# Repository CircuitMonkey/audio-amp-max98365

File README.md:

# audio-amp-max98365
Class-D audio amplifier using the Maxim MAX98365.  I2S input, 18W output.

## Features
MAX98365 Class-D Amplifier chip.  14W Max.
Dimensions:  20mm x 13mm
5-14V Supply Voltage
I2S Signal Input

## Images

## See Maxim Datasheet for additional information
[https://datasheets.maximintegrated.com/en/ds/MAX98365.pdf](https://datasheets.maximintegrated.com/en/ds/MAX98365.pdf)

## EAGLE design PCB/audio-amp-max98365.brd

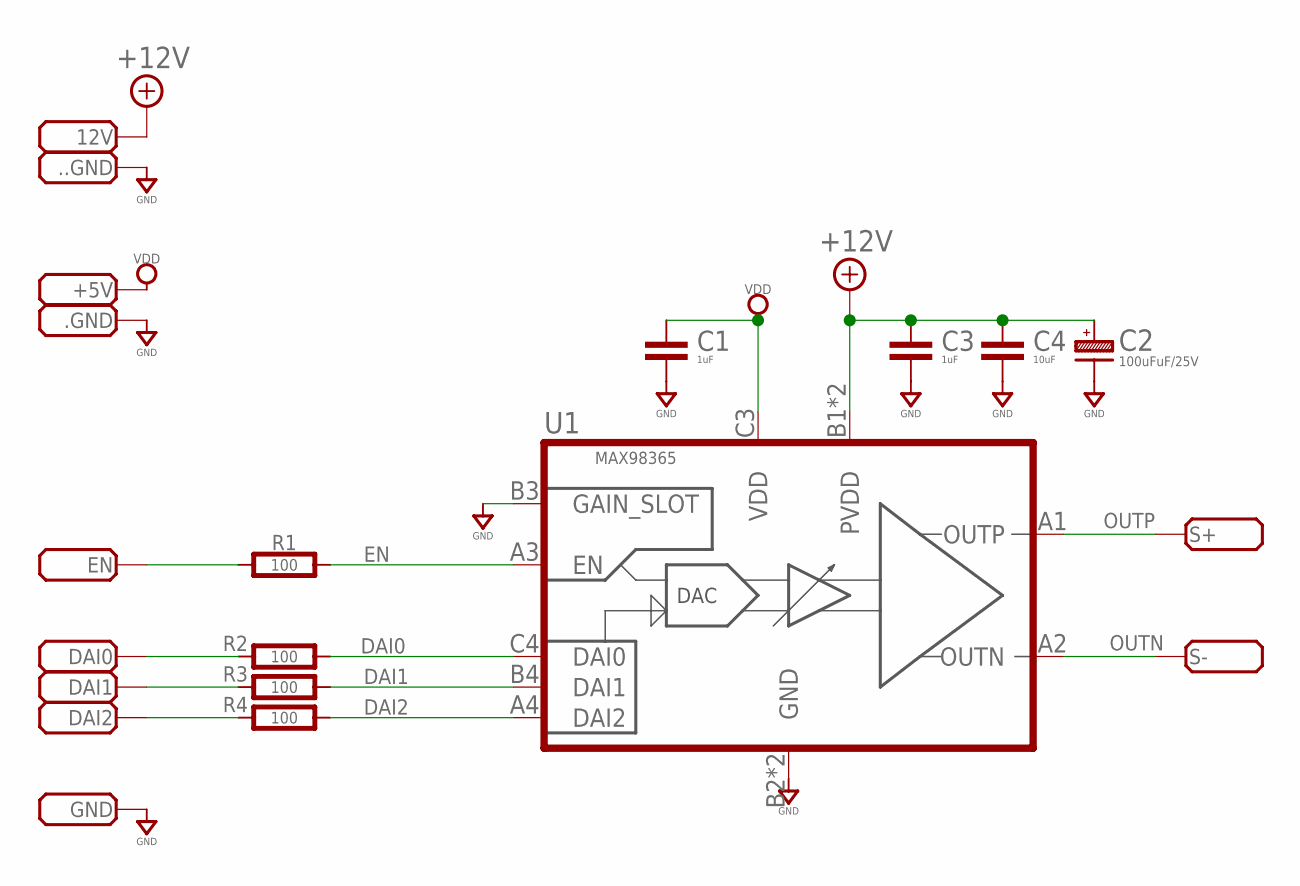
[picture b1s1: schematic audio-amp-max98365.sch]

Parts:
12V, ..GND, .GND: PADSMD-070X070; SMD-070MIL
+5V: PADSMD-070X070; SMD-070MIL
C1, C3: 1uF; 0603-CAP
C2: 100uFuF/25V; CAP_ALUM_SMT_6.3
C4: 10uF; 0603-CAP
DAI0, DAI1, DAI2: PADSMD-070X070; SMD-070MIL
EN: PADSMD-070X070; SMD-070MIL
GND: PADSMD-070X070; SMD-070MIL
R1, R2, R3, R4: 100; 0603-RES
S+: PADSMD-100X100; SMD-100X100
S-: PADSMD-100X100; SMD-100X100
U1: MAX98365; 12WLP

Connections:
+12V: 12V.1, C2.+, C3.1, C4.1, U1.B1 (PVDD), U1.C1 (PVDD)
DAI0: R2.2, U1.C4 (DAI0)
DAI1: R3.2, U1.B4 (DAI1)
DAI2: R4.2, U1.A4 (DAI2)
EN: R1.2, U1.A3 (EN)
GND: ..GND.1, .GND.1, C1.2, C2.- (N), C3.2, C4.2, GND.1, U1.B2 (GND), U1.B3 (GAIN_SLOT), U1.C2 (GND)
unnamed: EN.1, R1.1
unnamed: DAI0.1, R2.1
unnamed: DAI1.1, R3.1
unnamed: DAI2.1, R4.1
OUTN: S-.PAD, U1.A2 (OUTN)
OUTP: S+.PAD, U1.A1 (OUTP)
VDD: +5V.1, C1.1, U1.C3 (VDD)

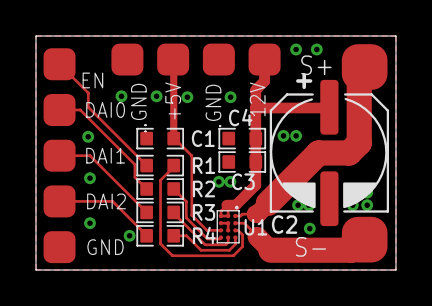
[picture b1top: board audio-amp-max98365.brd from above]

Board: 2 copper layers, 20.0 x 13.0 mm, 20 parts (0 on the bottom side), 13 nets.

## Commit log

2022-06-16 Rev.A Final
2022-06-16 Added BOM. Updated missing component values.
2022-06-16 Update README. Add PCB images.
2022-08-06 Added BOM
2022-08-30 Created PDF of schematic.
